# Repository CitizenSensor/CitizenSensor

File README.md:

# CitizenSensor Nitrate Measurement System

This repository contains all design files for the CitizenSensor nitrate measuring system.

## Repository Layout

```
+ 1_RaspberryPi-HAT/            Raspberry Pi HAT allowing electro-chemical measurements
| + Firmware/                   firmware for the ADuCM350 on the HAT
| + Hardware/                   PCB design files for the HAT
+ 2_Software/                   Main software running on the Raspberry Pi
+ 3_Electrometer/               PCB design files for the electrometer amplifier
+ 4_ConnectorBoard/             PCB design files for a small board to connect further components
+ 5_Enclosure/                  3D printable enclosure
+ 6_Accessories/                Additional helpful items
+ README.md                     this readme
```

## Documentation

Documentation can be found in the [CitizenSensor Wiki](https://github.com/CitizenSensor/CitizenSensor/wiki)

## Known Issues

See [Open Issues](https://github.com/CitizenSensor/CitizenSensor/issues?utf8=%E2%9C%93&q=is%3Aopen+is%3Aissue).

## License

The hardware documentation is licensed under CERN OHL v.1.2.

Software is licensed under GPLv3.

For details see licensing info in the respective sub directories.

---

Copyright FabLab München e.V. and Fraunhofer EMFT 2019-2020

CitizenSensor is sponsored by the Federal Ministry of Education and Research

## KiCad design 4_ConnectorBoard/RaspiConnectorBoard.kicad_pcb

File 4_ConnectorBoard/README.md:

# Connector Board

The connector board is a small PCB that sits on top of the CitizenSensor Raspberry Pi HAT and connects additional components to the Raspberry Pi, namely:

* HX711 breakout board to connect the load cell
* KY040 rotary encoder
* Motor for the magnetic stirrer

## Bill of Material

| Item | Description | Amount | Comment  |
| --- | --- | ---| ---  |
| J0 | Raspberry Pi Connector | 1 | 40 pins |
| J1 | Pin Header 90° 1x4 | 1 | 2.54 mm raster |
| J2 | Pin Header 90° 1x5 | 1 | 2.54 mm raster |
| J3 | Pin Header 90° 1x2 | 1 | 2.54 mm raster |
| R1 | 1K resistor | 1 | |
| D1 | 1N4004 diode| 1 | |
| Q1 | BC547| 1 | |

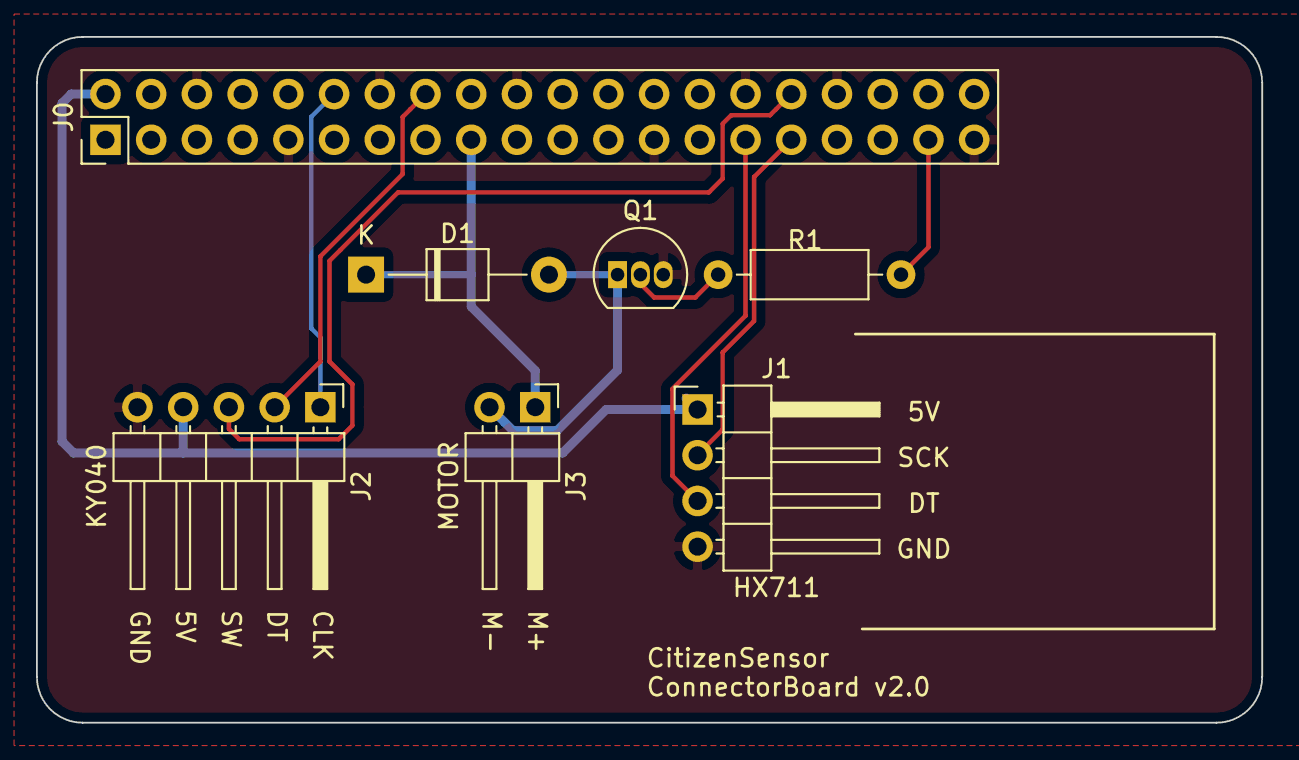
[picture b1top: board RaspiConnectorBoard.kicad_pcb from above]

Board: 2 copper layers, 68.1 x 38.1 mm, 7 parts (0 on the bottom side), 11 nets.

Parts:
D1: 1N4004; D_T-1_P10.16mm_Horizontal
J0: Raspberry_Pi_2_3; PinHeader_2x20_P2.54mm_Vertical
J1: HX711; PinHeader_1x04_P2.54mm_Horizontal
J2: KY040; PinHeader_1x05_P2.54mm_Horizontal
J3: MOTOR; PinHeader_1x02_P2.54mm_Horizontal
Q1: BC547; TO-92_Inline
R1: 1K; R_Axial_DIN0207_L6.3mm_D2.5mm_P10.16mm_Horizontal

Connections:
+3V3: D1.1, J0.17, J3.1
+5V: J0.2, J1.1, J2.4
GND: J0.6, J0.9, J0.14, J0.20, J0.25, J0.30, J0.34, J0.39, J1.4, J2.5, Q1.3
HX711_DT: J0.29, J1.3
HX711_SCK: J0.31, J1.2
KY040_CLK: J0.12, J2.1
KY040_DT: J0.16, J2.2
KY040_SW: J0.32, J2.3
MOTOR_PWM: J0.37, R1.2
unnamed: D1.2, J3.2, Q1.1
unnamed: Q1.2, R1.1

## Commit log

2019-10-30 initial commit, setting up directory structure
2019-10-30 added link to Wiki
2019-10-30 added connector board rev 2.0
2019-10-30 added enclosure stl files rev 2.0
2019-11-03 link to photo in wiki
2020-01-27 added pi software v200127
2020-01-27 updated license information
2020-01-27 add firmware for the Pi HAT v200127
2020-02-16 Create _Footer.md
    Initial commit
2020-02-16 Commit for first pull request
2020-02-16 Added soil sampling images, fixed links
2020-02-16 Fixed link to english article
2020-02-16 Fixed link to german article
2020-02-16 Fixed invalid link
2020-02-16 Add GPIO Connector Board overview, BOM and instructions to documentation #13
2020-02-16 fix table
2020-02-19 added enclosure STEP files
2020-02-19 added BOM
2020-02-24 added GerberFiles
2020-02-24 added qr code for düngebroschüre and added reset of HAT
2020-02-24 fixed path to main.py
2020-02-24 fixed spacings and database filename
2020-02-26 bug fixes
2020-02-26 changed qr resolution
2020-02-28 Added soil preparation images
2020-02-28 Added blank image
2020-02-28 First push of soil preparation documentation
2020-02-28 Fixed broken links between DE/EN docu
2020-02-28 Fixed broken links (part 2)
2020-03-01 Added further documentation content
2020-03-01 Fixed links
2020-03-01 Fixed link
2020-03-02 Added nitrate electrode
2020-03-02 added URL to datasheet of Nitrate electrode
2020-03-02 excerpt for dividing by zero at measurement routine
2020-03-04 added missing items to bom
2020-03-05 Added weight
2020-03-05 Changed cup amount to 5
    ISA, Calibration stock solution, calibration 4 ppm, calibration 100 ppm, sample solution
2020-03-05 fixed typo
2020-03-06 added cup_cap to 6_Accessories
2020-03-06 fixed hole dia
2020-03-07 Added new images
2020-03-07 Linked new images. Improved one image name.
2020-03-08 3 bilder von matthias (gerät offen)
2020-03-19 Added OpenSource information
2020-03-21 Updated OSS information
2020-04-07 separated ADI code and Citizensensor code
2020-04-07 Added soil sampling/preparation images
2020-04-07 Linked soil sampling/preparation images
2020-04-19 Added image: Bodenmühle
2020-05-02 Added Eagle files
2020-05-02 Add BOM
2020-07-06 main change
2020-07-09 changed ppm label to .2f float format
2020-07-18 Added localized Wiki texts (EN)
2020-07-18 Added localized texts - part 2
2020-07-25 Images for Aqueous Solution
2020-07-25 Documentation Aqueous Solution
2020-08-03 CS Orbital Shaker Initial Commit
2020-08-03 CS Orbital Shaker Readme edit
2020-10-21 Added assembly Wiki pages.
2020-10-21 Removed superfluous text.
2020-12-17 added fusion source files for enclosure
2022-02-09 changed averaging factor for scale to uneven number
2022-02-09 change weighing average factor to uneven number
2022-02-14 Update bom.md
    New ebay Links for plastic cups
2022-02-14 More detail on plastic cups
2022-02-15 changed some steps
